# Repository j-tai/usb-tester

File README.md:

# usb-tester

A simple device that checks if a USB cable is working, and whether the cable carries data or power only.

## Hardware

Powered by an STM32F0.

## Software

Powered by Rust and Embassy.

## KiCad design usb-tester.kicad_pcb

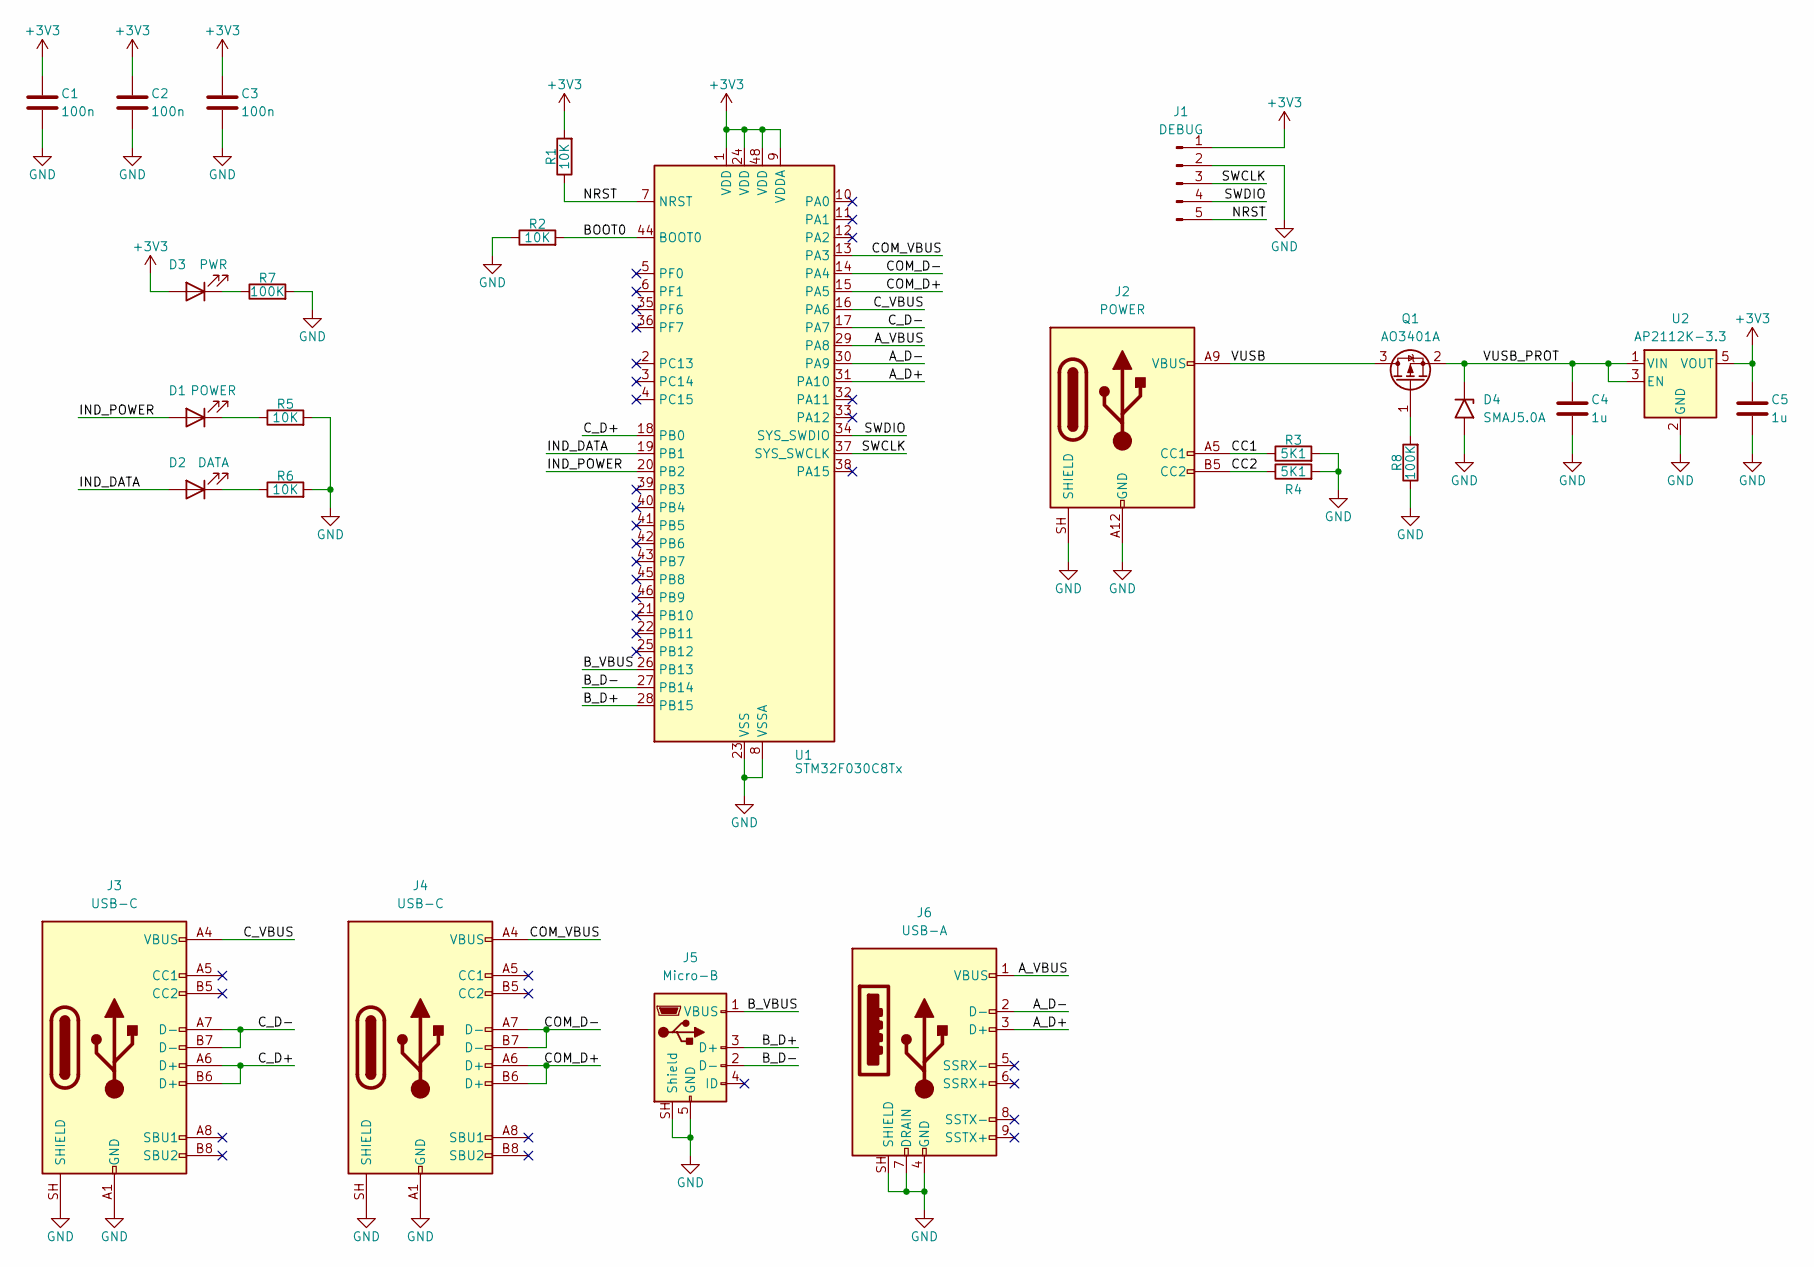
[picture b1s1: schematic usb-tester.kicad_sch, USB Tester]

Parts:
C1, C2, C3: 100n; C_0603_1608Metric_Pad1.08x0.95mm_HandSolder
C4, C5: 1u; C_0603_1608Metric_Pad1.08x0.95mm_HandSolder
D1: POWER; LED_0603_1608Metric_Pad1.05x0.95mm_HandSolder
D2: DATA; LED_0603_1608Metric_Pad1.05x0.95mm_HandSolder
D3: PWR; LED_0603_1608Metric_Pad1.05x0.95mm_HandSolder
D4: SMAJ5.0A; D_SMB
J1: DEBUG; JST_XH_B5B-XH-A_1x05_P2.50mm_Vertical
J2: POWER; USB_C_Receptacle_HRO_TYPE-C-31-M-17
J3, J4: USB-C; USB_C_Receptacle_HRO_TYPE-C-31-M-12
J5: Micro-B; USB_Micro-B_Wuerth_629105150521
J6: USB-A; USB3_A_Connector
Q1: AO3401A; SOT-23
R1, R2, R5, R6: 10K; R_0603_1608Metric_Pad0.98x0.95mm_HandSolder
R3, R4: 5K1; R_0603_1608Metric_Pad0.98x0.95mm_HandSolder
R7, R8: 100K; R_0603_1608Metric_Pad0.98x0.95mm_HandSolder
U1: STM32F030C8Tx; LQFP-48_7x7mm_P0.5mm
U2: AP2112K-3.3; SOT-23-5

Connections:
+3V3: C1.1, C2.1, C3.1, C5.1, D3.2 (A), J1.1, R1.2, U1.1 (VDD), U1.9 (VDDA), U1.24 (VDD), U1.48 (VDD), U2.5 (VOUT)
/A_D+: J6.3 (D+), U1.31 (PA10)
/A_D-: J6.2 (D-), U1.30 (PA9)
/A_VBUS: J6.1 (VBUS), U1.29 (PA8)
/BOOT0: R2.2, U1.44 (BOOT0)
/B_D+: J5.3 (D+), U1.28 (PB15)
/B_D-: J5.2 (D-), U1.27 (PB14)
/B_VBUS: J5.1 (VBUS), U1.26 (PB13)
/CC1: J2.A5 (CC1), R3.1
/CC2: J2.B5 (CC2), R4.1
/COM_D+: J4.A6 (D+), J4.B6 (D+), U1.15 (PA5)
/COM_D-: J4.A7 (D-), J4.B7 (D-), U1.14 (PA4)
/COM_VBUS: J4.A4 (VBUS), J4.A9 (VBUS), J4.B4 (VBUS), J4.B9 (VBUS), U1.13 (PA3)
/C_D+: J3.A6 (D+), J3.B6 (D+), U1.18 (PB0)
/C_D-: J3.A7 (D-), J3.B7 (D-), U1.17 (PA7)
/C_VBUS: J3.A4 (VBUS), J3.A9 (VBUS), J3.B4 (VBUS), J3.B9 (VBUS), U1.16 (PA6)
/IND_DATA: D2.2 (A), U1.19 (PB1)
/IND_POWER: D1.2 (A), U1.20 (PB2)
/NRST: J1.5, R1.1, U1.7 (NRST)
/SWCLK: J1.3, U1.37 (SYS_SWCLK)
/SWDIO: J1.4, U1.34 (SYS_SWDIO)
/VUSB: J2.A9 (VBUS), J2.B9 (VBUS), Q1.3 (D)
/VUSB_PROT: C4.1, D4.1 (A1), Q1.2 (S), U2.1 (VIN), U2.3 (EN)
GND: C1.2, C2.2, C3.2, C4.2, C5.2, D4.2 (A2), J1.2, J2.A12 (GND), J2.B12 (GND), J2.SH (SHIELD), J3.A1 (GND), J3.A12 (GND), J3.B1 (GND), J3.B12 (GND), J3.SH (SHIELD), J4.A1 (GND), J4.A12 (GND), J4.B1 (GND), J4.B12 (GND), J4.SH (SHIELD), J5.5 (GND), J5.SH (Shield), J6.4 (GND), J6.7 (DRAIN), J6.SH (SHIELD), R2.1, R3.2, R4.2, R5.2, R6.2, R7.2, R8.1, U1.8 (VSSA), U1.23 (VSS), U1.47 (VSS), U2.2 (GND)
unnamed: D1.1 (K), R5.1
unnamed: D2.1 (K), R6.1
unnamed: D3.1 (K), R7.1
unnamed: Q1.1 (G), R8.2

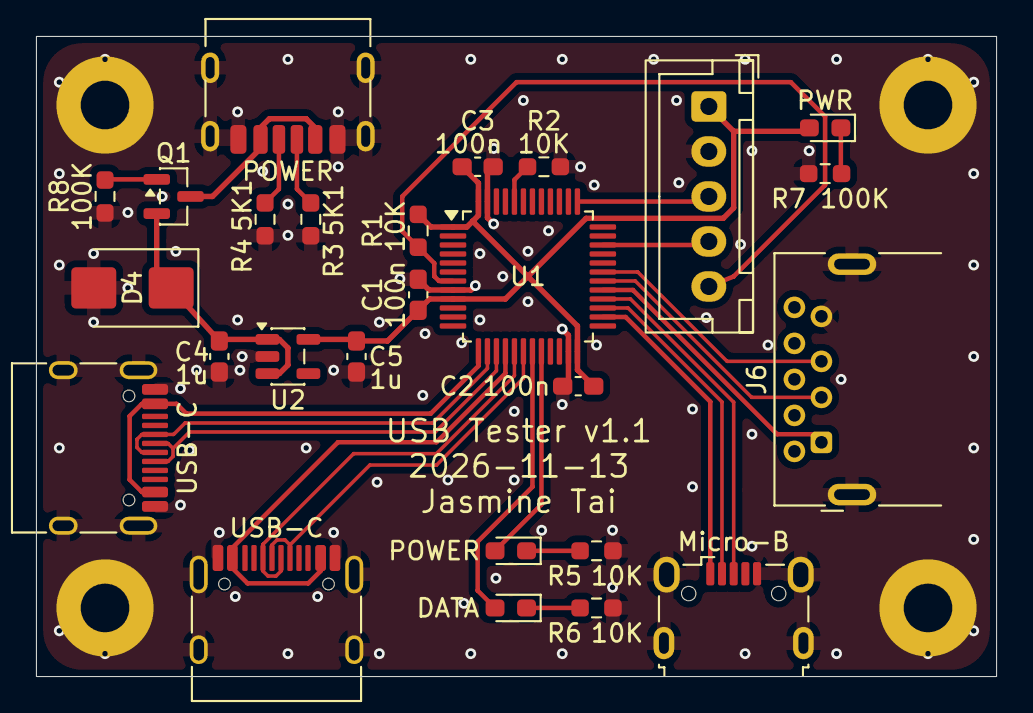
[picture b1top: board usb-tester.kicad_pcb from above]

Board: 2 copper layers, 53.3 x 35.6 mm, 26 parts (0 on the bottom side), 28 nets.

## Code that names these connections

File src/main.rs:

#![no_std]
#![no_main]

mod probe;

use defmt::info;
use defmt_rtt as _;
use embassy_executor::Spawner;
use embassy_stm32::gpio::{Flex, Level, Output, Pull, Speed};
use embassy_time::Timer;
use panic_probe as _;

use crate::probe::{Port, ProbeResult, probe};

#[embassy_executor::main]
async fn main(_spawner: Spawner) {
    let peri = embassy_stm32::init(Default::default());
    // Do not use these pins! They are reserved for debugging!
    let _swdio = peri.PA13;
    let _swclk = peri.PA14;

    info!("Hello, world!");

    let mut power_indicator = Output::new(peri.PB2, Level::Low, Speed::Low);
    let mut data_indicator = Output::new(peri.PB1, Level::Low, Speed::Low);

    let mut common = Port {
        power: Flex::new(peri.PA3),
        data_plus: Flex::new(peri.PA5),
        data_minus: Flex::new(peri.PA4),
    };

    let mut port_a = Port {
        power: Flex::new(peri.PA8),
        data_plus: Flex::new(peri.PA10),
        data_minus: Flex::new(peri.PA9),
    };

    let mut port_b = Port {
        power: Flex::new(peri.PB13),
        data_plus: Flex::new(peri.PB15),
        data_minus: Flex::new(peri.PB14),
    };

    let mut port_c = Port {
        power: Flex::new(peri.PA6),
        data_plus: Flex::new(peri.PB0),
        data_minus: Flex::new(peri.PA7),
    };

    for port in [&mut common, &mut port_a, &mut port_b, &mut port_c] {
        for pin in port.pins() {
            pin.set_as_input(Pull::Up);
        }
    }

    loop {
        let ProbeResult { power, data } = probe(&mut common, &mut port_a).await
            | probe(&mut common, &mut port_b).await
            | probe(&mut common, &mut port_c).await
            | probe(&mut port_a, &mut port_b).await
            | probe(&mut port_a, &mut port_c).await
            | probe(&mut port_b, &mut port_c).await;

        power_indicator.set_level(power.into());
        data_indicator.set_level(data.into());
        Timer::after_millis(200).await;
    }
}

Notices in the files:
usb-tester.kicad_pcb:
Copyright © 2026 ${COMPANY}. All rights reserved.
